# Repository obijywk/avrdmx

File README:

avrdmx is an implementation of multi-universe DMX output using Atmel AVR
microcontrollers. It's able to output up to 4 universes of DMX simultaneously
from a single device, without using hardware UARTs - this reduces hardware
complexity and cost. This project consists of a driver program that runs on a
host computer, firmware that runs on a board containing an Atmel AVR
microcontroller, and hardware containing RS-485 driver chips for sending data
to DMX receivers.

driver/ contains the Python driver program.  It receives streaming ACN packets
via UDP, and sends channel data to an Atmel AVR board attached via USB (using
USB CDC serial port emulation).

firmware/ contains an Atmel AVR program designed to run on a Teensy++ 2.0 board
(based on the AT90USB1286).

leonardo_firmware/ contains an Atmel AVR program designed to run on an Arduino
Leonardo (based on the ATmega32u4). It's based on LUFA
(http://www.fourwalledcubicle.com/LUFA.php).

Both firmware programs receive and buffer channel data from the driver program,
and output multiple universes of DMX to physical pins.

pcb/ contains an Eagle CAD design for an Arduino shield that uses RS-485 driver
chips to drive DMX receivers. It's intended to be used in conjunction with the
leonardo_firmware.

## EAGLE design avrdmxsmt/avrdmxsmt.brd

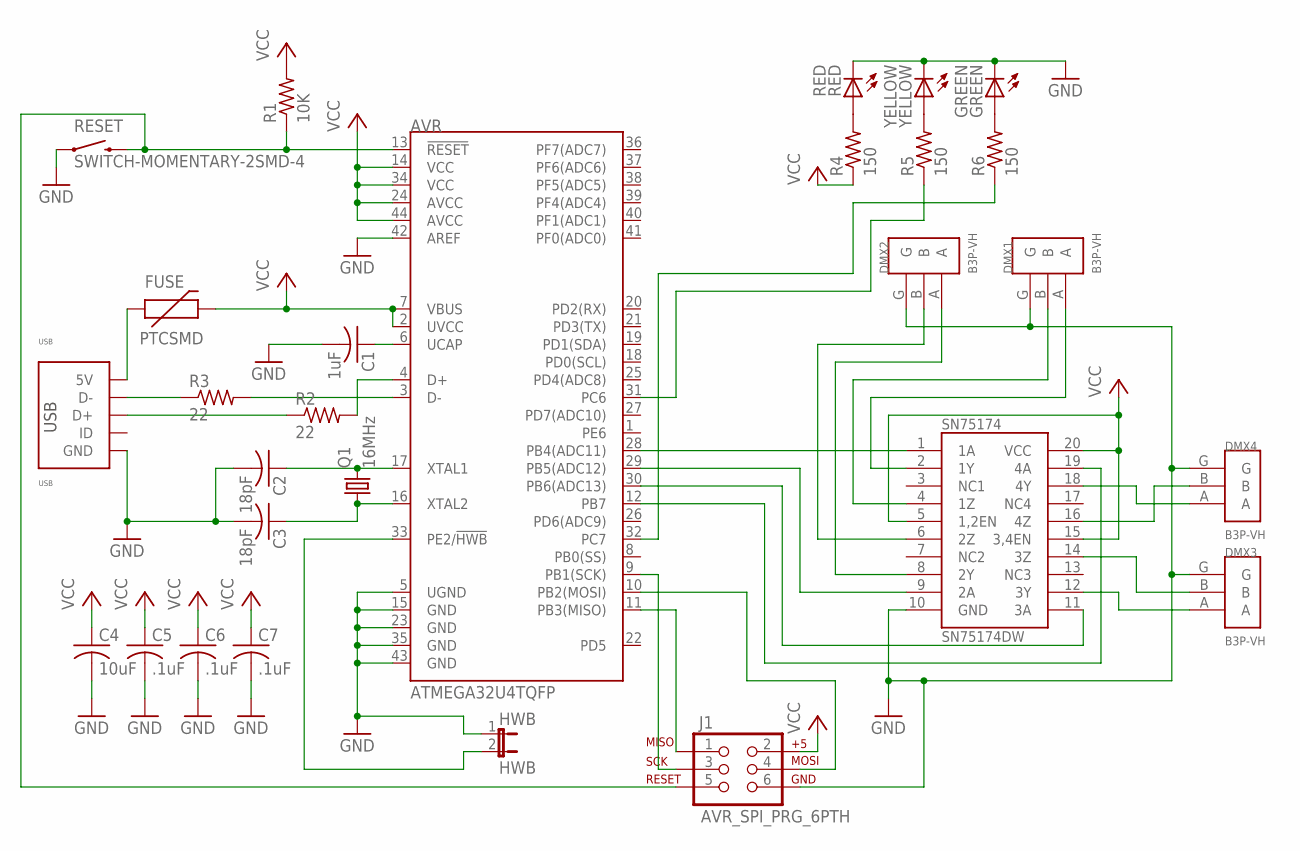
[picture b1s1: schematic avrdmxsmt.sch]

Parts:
AVR: ATMEGA32U4TQFP; SPARKFUN-DIGITALIC_TQFP44
C1: 1uF; C0603K
C2, C3: 18pF; C0603K
C4: 10uF; C0603K
C5, C6, C7: .1uF; C0603K
DMX1, DMX2, DMX3, DMX4: B3P-VH
FUSE: PTCSMD; PTC-1206
GREEN: GREEN; LED-0603
HWB: HWB; 1X02
J1: AVR_SPI_PRG_6PTH; 2X3
Q1: 16MHz; SM49
R1: 10K; R0603
R2, R3: 22; R0603
R4, R5, R6: 150; R0603
RED: RED; LED-0603
RESET: SWITCH-MOMENTARY-2SMD-4; TACTILE_SWITCH_TALL
SN75174: SN75174DW; SOIC20R
USB: USB; 10118193-0001LF
YELLOW: YELLOW; LED-0603

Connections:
GND: AVR.5 (UGND), AVR.15 (GND), AVR.23 (GND), AVR.35 (GND), AVR.42 (AREF), AVR.43 (GND), C1.2, C2.2, C3.2, C4.2, C5.2, C6.2, C7.2, DMX1.G, DMX2.G, DMX3.G, DMX4.G, GREEN.C, HWB.1, J1.6, RED.C, RESET.A2 (1), SN75174.10 (GND), USB.5 (GND), USB.S1 (GND), USB.S2 (GND), USB.S3 (GND), USB.S4 (GND), YELLOW.C
unnamed: AVR.13 (!RESET), J1.5, R1.1, RESET.B2 (2)
unnamed: AVR.3 (D-), R3.2
unnamed: R3.1, USB.2 (D-)
unnamed: AVR.4 (D+), R2.2
unnamed: R2.1, USB.3 (D+)
unnamed: FUSE.1, USB.1 (5V)
unnamed: AVR.6 (UCAP), C1.1
unnamed: AVR.17 (XTAL1), C2.1, Q1.2
unnamed: AVR.16 (XTAL2), C3.1, Q1.1
unnamed: AVR.28 (PB4(ADC11)), SN75174.1 (1A)
unnamed: AVR.29 (PB5(ADC12)), SN75174.9 (2A)
unnamed: AVR.30 (PB6(ADC13)), SN75174.11 (3A)
unnamed: AVR.12 (PB7), SN75174.19 (4A)
unnamed: DMX1.A, SN75174.2 (1Y)
unnamed: DMX1.B, SN75174.4 (1Z)
unnamed: DMX2.A, SN75174.8 (2Y)
unnamed: DMX2.B, SN75174.6 (2Z)
unnamed: DMX3.A, SN75174.12 (3Y)
unnamed: DMX3.B, SN75174.14 (3Z)
unnamed: DMX4.A, SN75174.18 (4Y)
unnamed: DMX4.B, SN75174.16 (4Z)
unnamed: R4.2, RED.A
unnamed: R5.2, YELLOW.A
unnamed: GREEN.A, R6.2
unnamed: AVR.33 (PE2/!HWB), HWB.2
unnamed: AVR.32 (PC7), R6.1
unnamed: AVR.31 (PC6), R5.1
unnamed: AVR.10 (PB2(MOSI)), J1.4
unnamed: AVR.11 (PB3(MISO)), J1.1
unnamed: AVR.9 (PB1(SCK)), J1.3
VCC: AVR.2 (UVCC), AVR.7 (VBUS), AVR.14 (VCC), AVR.24 (AVCC), AVR.34 (VCC), AVR.44 (AVCC), C4.1, C5.1, C6.1, C7.1, FUSE.2, J1.2, R1.2, R4.1, SN75174.5 (1,2EN), SN75174.15 (3,4EN), SN75174.20 (VCC)

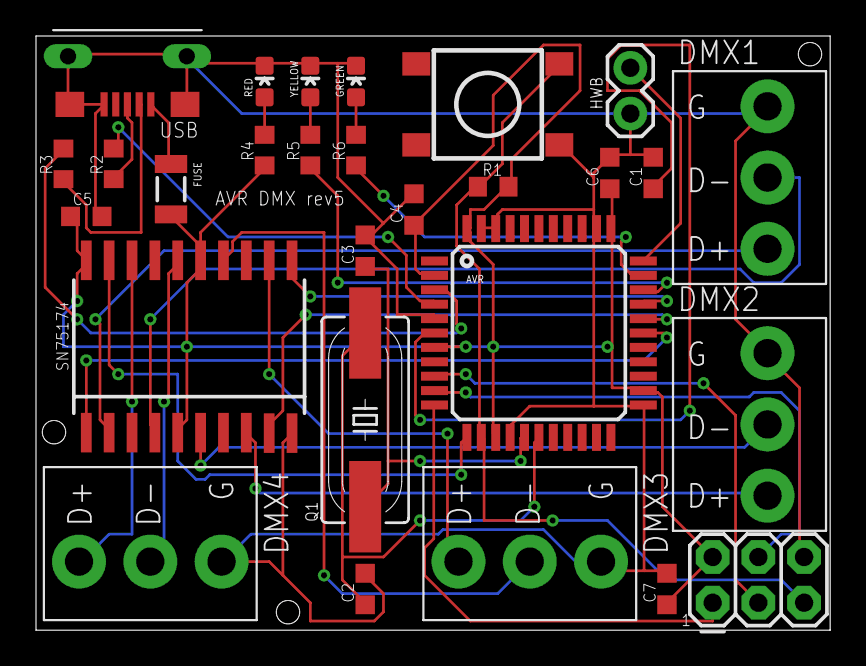
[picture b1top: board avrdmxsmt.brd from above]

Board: 2 copper layers, 44.1 x 33.0 mm, 28 parts (0 on the bottom side), 32 nets.

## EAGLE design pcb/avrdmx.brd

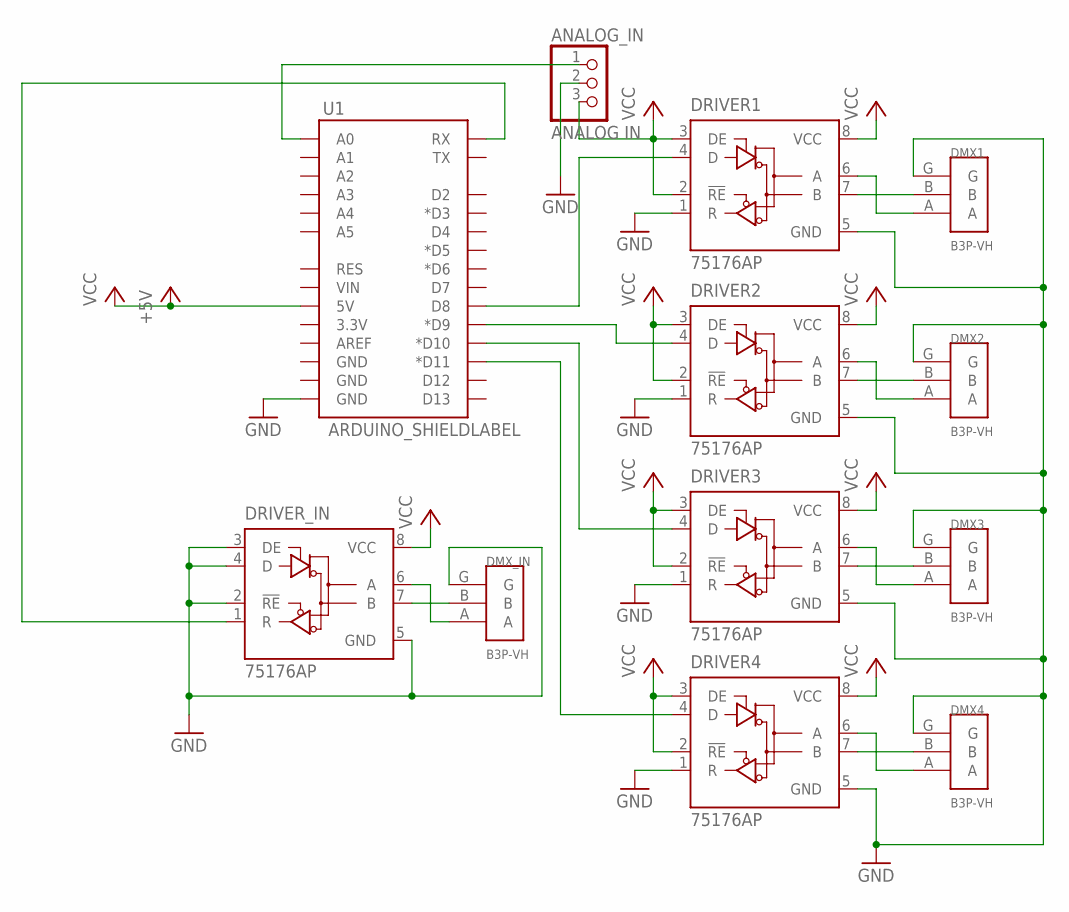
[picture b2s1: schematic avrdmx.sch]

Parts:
ANALOG_IN: ANALOG IN; 1X03
DMX1, DMX2, DMX3, DMX4: B3P-VH
DMX_IN: B3P-VH
DRIVER1, DRIVER2, DRIVER3, DRIVER4: 75176AP; DIL08
DRIVER_IN: 75176AP; DIL08
U1: ARDUINO_SHIELDLABEL; DUEMILANOVE_SHIELD

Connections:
GND: ANALOG_IN.2, DMX1.G, DMX2.G, DMX3.G, DMX4.G, DMX_IN.G, DRIVER1.1 (R), DRIVER1.5 (GND), DRIVER2.1 (R), DRIVER2.5 (GND), DRIVER3.1 (R), DRIVER3.5 (GND), DRIVER4.1 (R), DRIVER4.5 (GND), DRIVER_IN.2 (!RE), DRIVER_IN.3 (DE), DRIVER_IN.4 (D), DRIVER_IN.5 (GND), U1.GND@0 (GND)
unnamed: DRIVER1.4 (D), U1.D8
unnamed: DRIVER2.4 (D), U1.D9 (*D9)
unnamed: DRIVER3.4 (D), U1.D10 (*D10)
unnamed: DRIVER4.4 (D), U1.D11 (*D11)
unnamed: ANALOG_IN.1, U1.A0
unnamed: DMX_IN.B, DRIVER_IN.7 (B)
unnamed: DMX1.B, DRIVER1.7 (B)
unnamed: DRIVER_IN.1 (R), U1.RX
unnamed: DMX1.A, DRIVER1.6 (A)
unnamed: DMX2.B, DRIVER2.7 (B)
unnamed: DMX2.A, DRIVER2.6 (A)
unnamed: DMX3.B, DRIVER3.7 (B)
unnamed: DMX3.A, DRIVER3.6 (A)
unnamed: DMX4.A, DRIVER4.6 (A)
unnamed: DMX4.B, DRIVER4.7 (B)
unnamed: DMX_IN.A, DRIVER_IN.6 (A)
VCC: ANALOG_IN.3, DRIVER1.2 (!RE), DRIVER1.3 (DE), DRIVER1.8 (VCC), DRIVER2.2 (!RE), DRIVER2.3 (DE), DRIVER2.8 (VCC), DRIVER3.2 (!RE), DRIVER3.3 (DE), DRIVER3.8 (VCC), DRIVER4.2 (!RE), DRIVER4.3 (DE), DRIVER4.8 (VCC), DRIVER_IN.8 (VCC), U1.5V

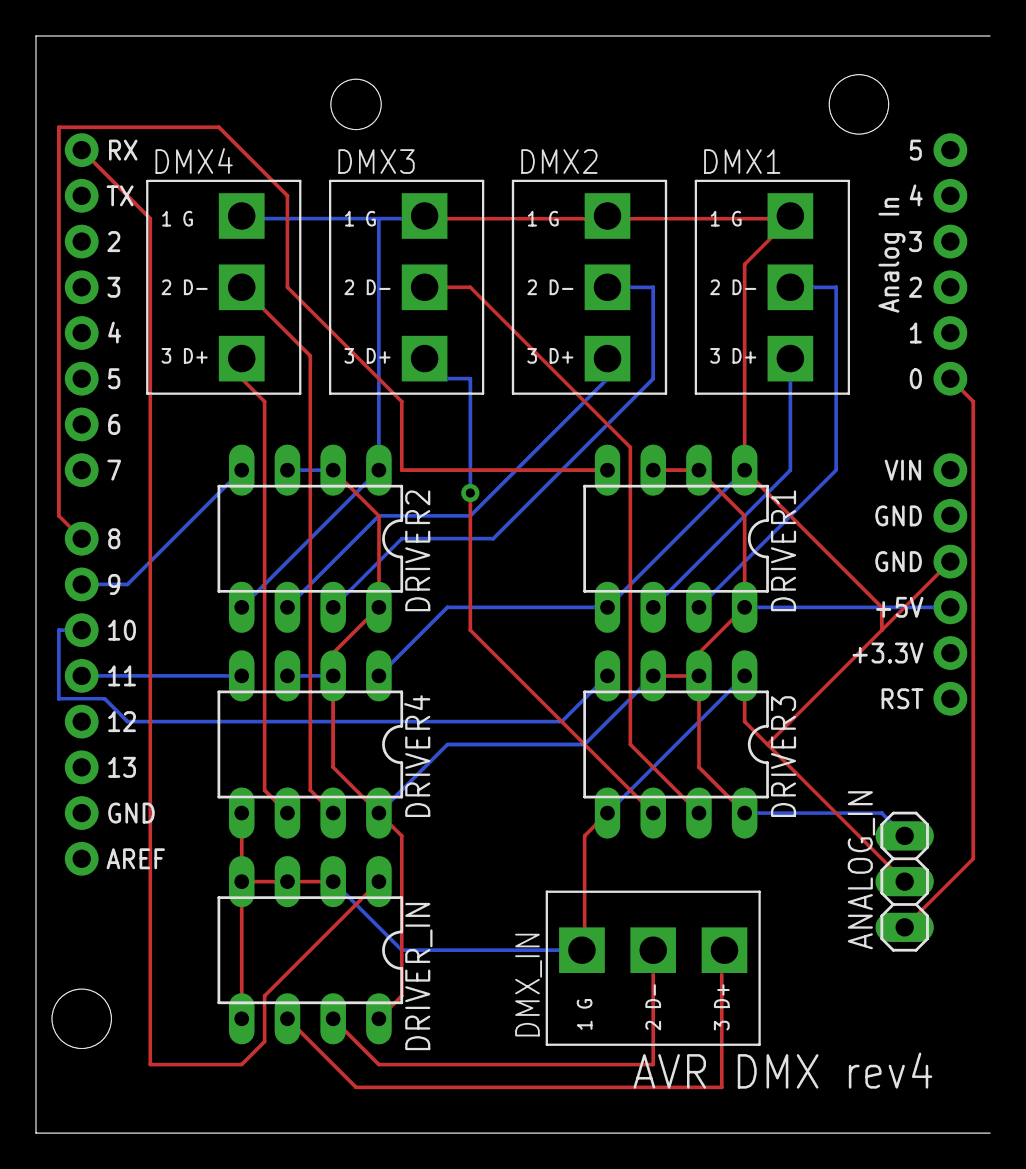
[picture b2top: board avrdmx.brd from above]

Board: 2 copper layers, 53.0 x 60.9 mm, 12 parts (0 on the bottom side), 18 nets.

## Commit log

2010-12-23 Initial commit (README)
2010-12-23 Initial commit of work in progress dmx output
2010-12-23 Fix assembly to follow C calling conventions Fix timer interrupts
2010-12-24 started implementing streaming ACN receiver
2010-12-24 implemented more flexible sACN packet parser
2010-12-24 sACN should ignore non-DMX packets busy-looping used 100% cpu on windows
2010-12-24 interrupt handler should save SREG
2010-12-25 some assembly bugfixes and optimizations
2010-12-25 remove -save-temps compile option
2010-12-25 renamed and reorganized some files
2010-12-25 implement serial output driver program (and unix-only test)
2010-12-26 implement top-level driver program fix sACN to work correctly with multiple universes
2010-12-26 add USB receive support to firmware
2010-12-30 minor fixes to get it to work
2011-10-31 lock channel
2012-09-23 Added rev1 pcb design
2012-09-23 switched from arduino pins 2-5 to 8-11
2012-09-24 initial commit of leonardo firmware
2012-09-24 board rev3 - fix 7404N Vcc and GND
2012-09-28 changed assembly to use timers
2012-09-28 more timing improvement - replace some NOPs with hardware timer delay
2012-09-28 fix COMPA routine to not need to save SREG, saves some cycles!
2012-10-01 sacn receiver detects protocol version using vector
2012-10-02 lots of driver and firmware cleanup, to get everything working with leonardo
2012-10-02 added test pattern mode to firmware
2012-10-05 configurable framerate
2012-10-05 updating driver to work on windows
2012-10-05 improving usb performance
2012-10-06 temporary - send fake data fast
2012-10-06 cleanup
2012-10-12 My changes that I think might be bad. dont trust them.
2012-10-29 fix concurrent serial write bug
2013-09-25 add midi cue sending from driver program
2014-03-16 schematic changes from a long time ago, not sure if they're good
2014-03-16 old driver updates, not sure if they're useful
2014-03-16 more old schematic changes, not sure if they're good
2014-03-16 finish PCB rev3
2014-04-01 fix leonardo_firmware for new versions of LUFA
2014-04-02 fix driver program merge conflict
2014-04-02 PCB rev4 - fixes: - larger holes for DMX cable headers - fix receiver driver wiring - better labels
2014-04-24 gitignore
2014-04-24 initial work on qtdriver
2014-04-24 standalone surface mount PCB for avrdmx
2014-04-25 qtdriver dmx output
2014-04-29 midi go cue support
2014-05-01 SMT board cleanup
2014-05-03 mark avr isp header pin 1
2014-05-05 ignore serial.tools if not found
2014-05-05 add dimmer check better blinky lights
2014-05-05 display channel check value
2014-05-06 surface mount PCB drill sizes, cleanup
2015-01-25 create a LUFA USER board for the AVR DMX SMT board in the leonardo firmware

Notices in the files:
parts and their libraries:
SparkFun-DigitalIC: Licensing: Creative Commons ShareAlike 4.0 International - https://creativecommons.org/licenses/by-sa/4.0
SparkFun-Boards: Licensing: CC v3.0 Share-Alike You are welcome to use this library for commercial purposes.
